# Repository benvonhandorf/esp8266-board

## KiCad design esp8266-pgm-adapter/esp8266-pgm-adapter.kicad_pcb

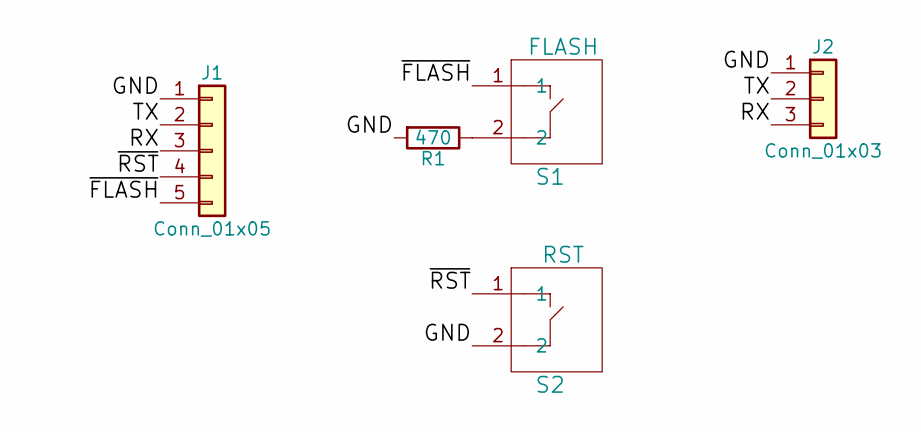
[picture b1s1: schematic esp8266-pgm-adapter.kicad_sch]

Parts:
J1: Conn_01x05; Pin_Header_Straight_1x05_Pitch2.54mm
J2: Conn_01x03; Pin_Header_Straight_1x03_Pitch2.54mm
R1: 470; R_0805_HandSoldering
S1: FLASH; TacButton_6mm_6mm
S2: RST; TacButton_6mm_6mm

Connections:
/GND: J1.1, J2.1, R1.2, S2.2
/RX: J1.3, J2.3
/TX: J1.2, J2.2
/~FLASH: J1.5, S1.1
/~RST: J1.4, S2.1
unnamed: R1.1, S1.2

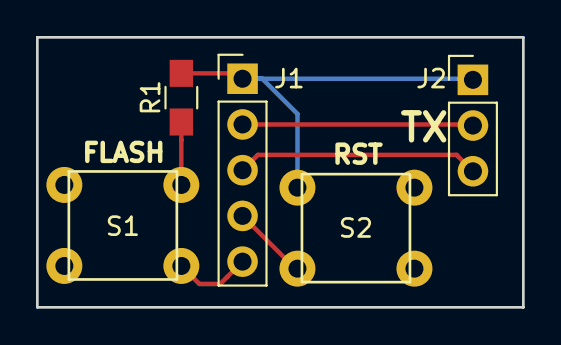
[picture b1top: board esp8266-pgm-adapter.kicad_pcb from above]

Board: 2 copper layers, 27.0 x 15.0 mm, 5 parts (0 on the bottom side), 6 nets.

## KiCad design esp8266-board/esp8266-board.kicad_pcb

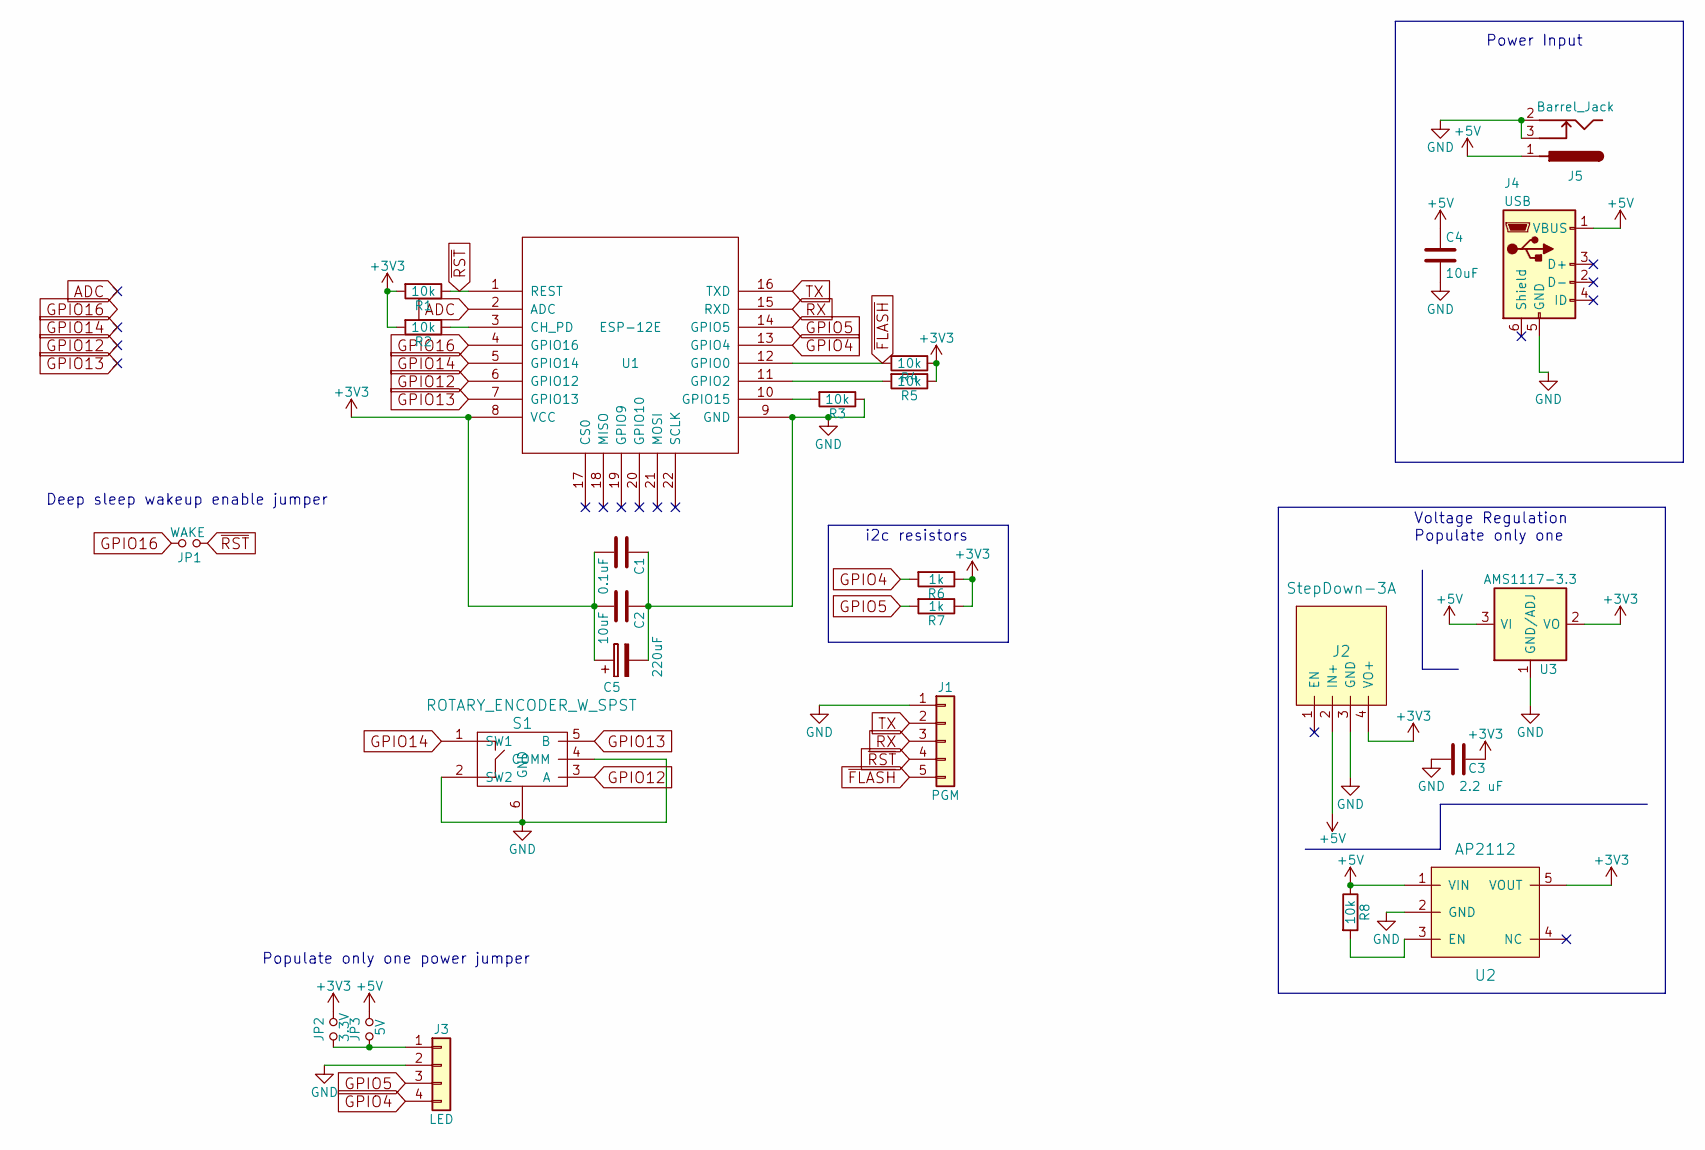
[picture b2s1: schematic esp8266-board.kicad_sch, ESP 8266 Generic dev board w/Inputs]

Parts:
C1: 0.1uF; C_1206_HandSoldering
C2, C4: 10uF; C_1206_HandSoldering
C3: 2.2 uF; C_1206_HandSoldering
C5: 220uF; CP_Tantalum_Case-B_EIA-3528-21_Hand
J1: PGM; Pin_Header_Straight_1x05_Pitch2.54mm
J2: StepDown-3A; SwitchingRegulator_Selectable
J3: LED; Pin_Header_Straight_1x04_Pitch2.54mm
J4: USB; USB_Micro-B
J5: Barrel_Jack; 5.5mm_Barrel_Jack
JP1: WAKE; SolderJumper
JP2: 3.3V; SolderJumper
JP3: 5V; SolderJumper
R1, R2, R3, R4, R5, R8: 10k; R_1206_HandSoldering
R6, R7: 1k; R_0805_HandSoldering
S1: ROTARY_ENCODER_W_SPST; Rotary_Encoder_Or_Switch
U1: ESP-12E
U2: AP2112; SOT-23-5
U3: AMS1117-3.3; SOT-223

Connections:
+3V3: C1.2, C2.2, C3.1, C5.1, J2.4 (VO+), JP2.2, R1.2, R2.2, R4.1, R5.1, R6.1, R7.1, U1.8 (VCC), U2.5 (VOUT), U3.2 (VO), U3.4 (VO)
+5V: C4.1, J2.2 (IN+), J4.1 (VBUS), J5.1, JP3.2, R8.1, U2.1 (VIN), U3.3 (VI)
ADC: U1.2 (ADC)
GND: C1.1, C2.1, C3.2, C4.2, C5.2, J1.1, J2.3 (GND), J3.2, J4.5 (GND), J5.2, J5.3, R3.1, S1.2 (SW2), S1.4 (COMM), S1.6 (GND), U1.9 (GND), U2.2 (GND), U3.1 (GND/ADJ)
GPIO4: J3.4, R6.2, U1.13 (GPIO4)
GPIO5: J3.3, R7.2, U1.14 (GPIO5)
GPIO12: S1.3 (A), U1.6 (GPIO12)
GPIO13: S1.5 (B), U1.7 (GPIO13)
GPIO14: S1.1 (SW1), U1.5 (GPIO14)
GPIO16: JP1.2, U1.4 (GPIO16)
unnamed: J3.1, JP2.1, JP3.1
unnamed: R2.1, U1.3 (CH_PD)
unnamed: R3.2, U1.10 (GPIO15)
unnamed: R5.2, U1.11 (GPIO2)
unnamed: R8.2, U2.3 (EN)
RX: J1.3, U1.15 (RXD)
TX: J1.2, U1.16 (TXD)
~FLASH: J1.5, R4.2, U1.12 (GPIO0)
~RST: J1.4, JP1.1, R1.1, U1.1 (REST)

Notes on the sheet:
i2c resistors
Populate only one power jumper
Deep sleep wakeup enable jumper
Voltage Regulation Populate only one
Power Input

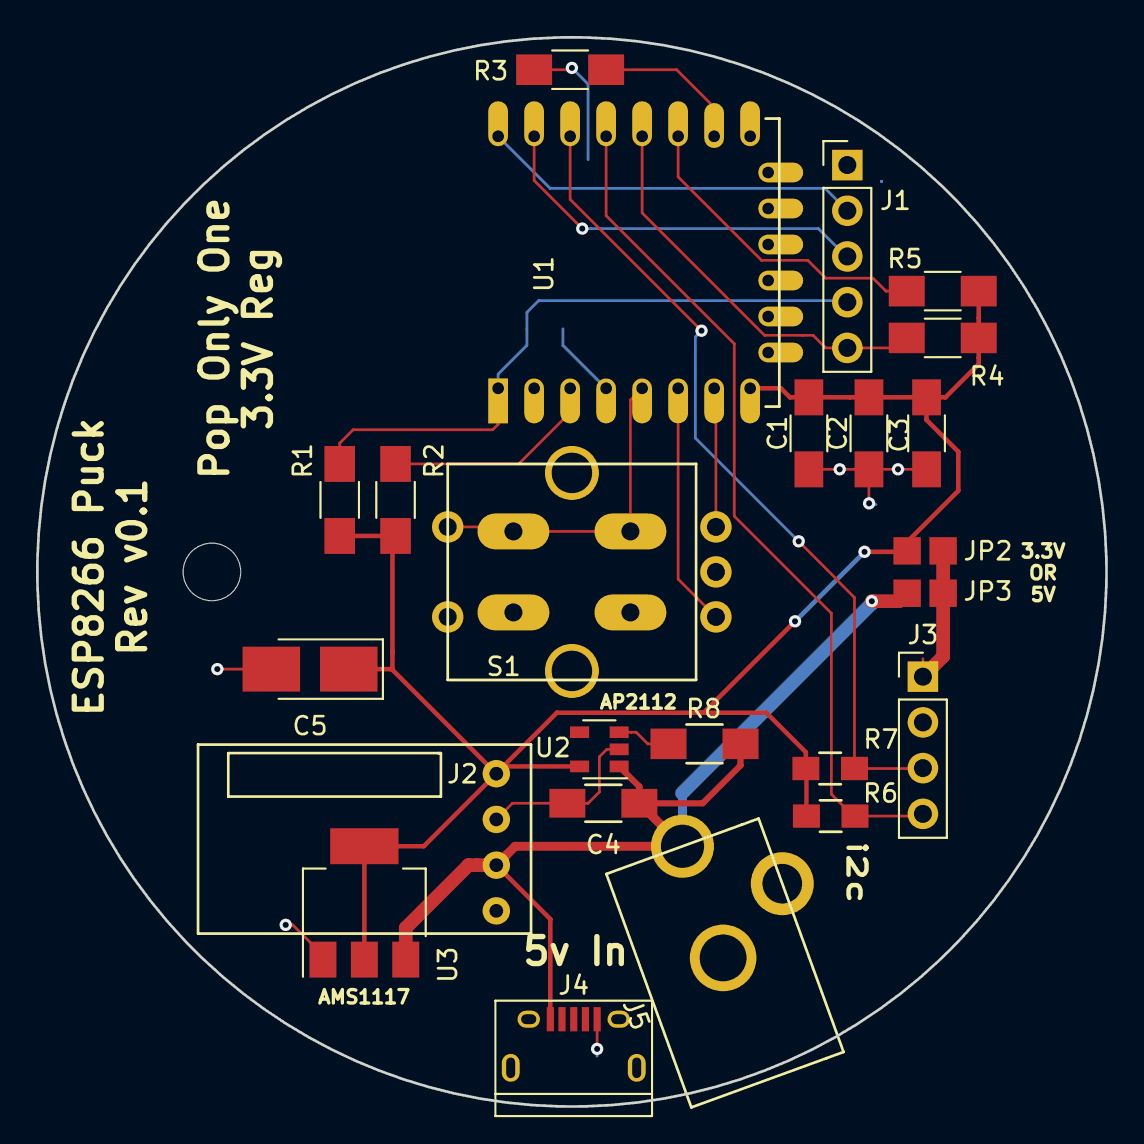
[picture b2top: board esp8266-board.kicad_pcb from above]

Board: 2 copper layers, 59.4 x 59.4 mm, 25 parts (1 on the bottom side), 18 nets.

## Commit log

2017-11-06 Added esp8266 kicad submodule
2017-11-06 Submodule dance, done better I hope
2017-11-06 Kicad created
2017-11-11 Reogranizing and making use of new footprints
2017-11-16 New voltage regulation structure in process
2017-11-27 First board rev order 0.1
2017-12-11 Fixes to esp board, programming header

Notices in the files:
esp8266-board/esp8266-board.kicad_sch:
MIT License
